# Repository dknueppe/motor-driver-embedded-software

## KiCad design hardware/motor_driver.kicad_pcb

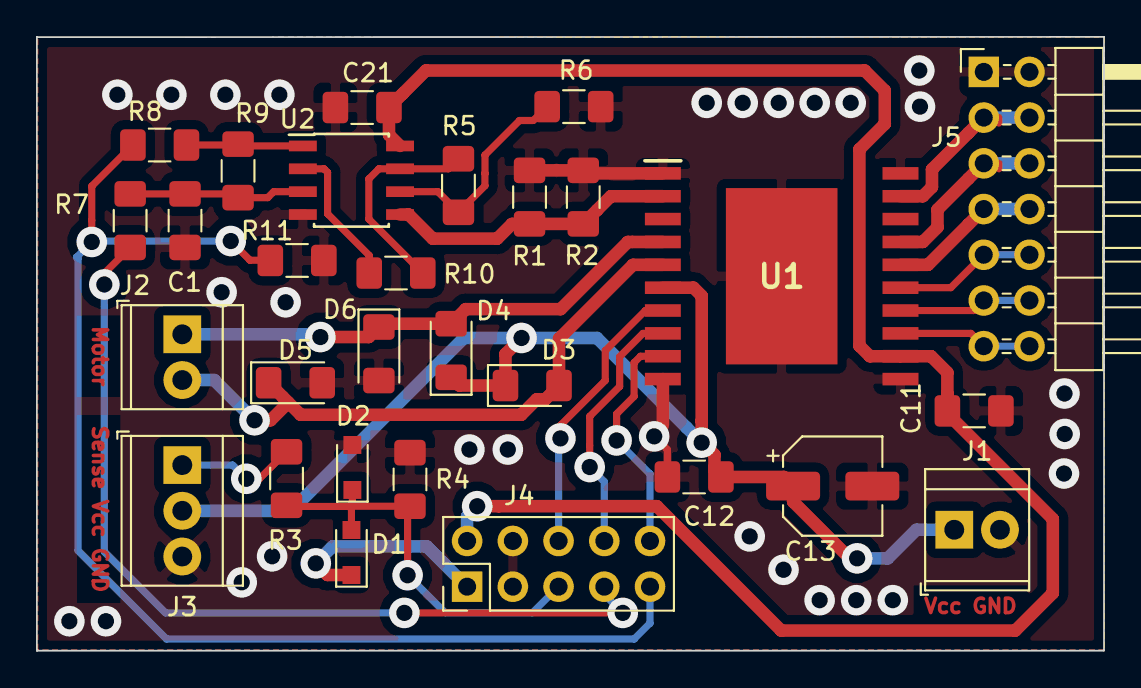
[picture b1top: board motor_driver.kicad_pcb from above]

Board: 2 copper layers, 59.3 x 34.1 mm, 29 parts (0 on the bottom side), 25 nets.

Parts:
C1: 16n; C_1206_3216Metric_Pad1.42x1.75mm_HandSolder
C11, C12, C21: 100n; C_1206_3216Metric_Pad1.42x1.75mm_HandSolder
C13: 10u; CP_Elec_5x4.5
D1, D2: D_Schottky; D_SOD-323_HandSoldering
D3, D4, D5, D6: D; D_1206_3216Metric_Pad1.42x1.75mm_HandSolder
J1, J2: Screw_Terminal_01x02; TerminalBlock_TE_282834-2_1x02_P2.54mm_Horizontal
J3: Screw_Terminal_01x03; TerminalBlock_TE_282834-3_1x03_P2.54mm_Horizontal
J4: Conn_02x05_Odd_Even; PinHeader_2x05_P2.54mm_Vertical
J5: Extension; PinHeader_2x07_P2.54mm_Horizontal
R1, R2: 200m; R_1206_3216Metric_Pad1.42x1.75mm_HandSolder
R3: 2.7k; R_1206_3216Metric_Pad1.42x1.75mm_HandSolder
R4, R6, R7, R10: 1k; R_1206_3216Metric_Pad1.42x1.75mm_HandSolder
R5, R11: 9k; R_1206_3216Metric_Pad1.42x1.75mm_HandSolder
R8: 4.7k; R_1206_3216Metric_Pad1.42x1.75mm_HandSolder
R9: 14.3k; R_1206_3216Metric_Pad1.42x1.75mm_HandSolder
U1: L298P; SOIC127P1420X360-21N
U2: LMV358; SOIC-8_3.9x4.9mm_P1.27mm

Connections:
+3V3: D1.1, J4.1
+5V: C11.1, C21.1, J4.2, U1.12, U2.8
+12V: C12.1, C13.1, D3.1, D4.1, J1.1, J3.2, U1.6
/COMP_IN: J4.7, R7.1
/COMP_OUT: J4.9, R8.2, R11.1
/ENABLE: J4.8, U1.8
/ENABLE_B: J5.11, J5.12, U1.14
/INPUT1: J4.6, U1.7
/INPUT2: J4.10, U1.9
/INPUT4: J5.9, J5.10, U1.15
/INPUT_3: J5.13, J5.14, U1.13
/OUT3: J5.7, J5.8, U1.16
/OUT4: J5.5, J5.6, U1.17
/PROX_OUT: D1.2, D2.1, J4.5, R3.2, R4.1
/SENSE_B: J5.3, J5.4, U1.19
GND: C1.2, C11.2, C12.2, C13.2, C21.2, D2.2, D5.2, D6.2, J1.2, J3.3, J4.3, J4.4, J5.1, J5.2, R1.2, R2.2, R4.2, R6.1, R11.2, U1.1, U1.10, U1.11, U1.20, U1.21, U2.4
unnamed: C1.1, R7.2, R9.2, U2.3
unnamed: D3.2, D5.1, J2.2, U1.5
unnamed: D4.2, D6.1, J2.1, U1.4
unnamed: J3.1, R3.1
unnamed: R1.1, R2.1, U1.2, U2.5
unnamed: R5.1, R6.2, U2.6
unnamed: R8.1, R9.1, U2.1
unnamed: R10.1, U2.2
unnamed: R5.2, R10.2, U2.7

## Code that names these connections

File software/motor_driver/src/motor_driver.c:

#include <wiringPi.h>
#include <stdio.h>
#include <stdbool.h>
#include <unistd.h>
#include "TimerObservable.h"
#include "PinObserver.h"
#include "PinObservable.h"
#include "FreqCounter.h"

/* Pin assignments from motor driver board to wiringPi internals */
#define INPUT1      3   /* connect YELLOW Wire with physical pin 15 (eigth on the inner row) */
#define INPUT2      5   /* connect RED Wire with physical pin 18 (ninth on the outer row) */
#define ENABLE      4   /* connect ORANGE Wire with physical pin 16 (eigth on the outer row) */
#define PROX_OUT    7   /* connect VIOLET Wire with physical pin 7 (fourth on the inner row) */
#define COMP_IN     1   /* connect BLUE Wire with physical pin 12 (sixth on the outer row) */
#define COMP_OUT    2   /* connect GREEN Wire with physical pin 13 (seventh on the inner row) */

int main()
{
    wiringPiSetup();

/* driving the motor */
    TimerObservable pwm = newTimerObservable(PWM_ENABLE);
    pwm->frequency = 440;
    pwm->dutyCycle = 100;
    PinObserver in1 = newPinObserver(INPUT1, LOW);
    PinObserver in2 = newPinObserver(INPUT2, LOW);
    pwm->clazz->observe((Observable)pwm, (void*)in1);
    pwm->clazz->start(pwm);

/* setup proximity sensor */
    PinObservable proximity_sensor = newPinObservable(PROX_OUT);
    FreqCounter freq_counter = newFreqCounter();
    proximity_sensor->clazz->observe((Observable)proximity_sensor, (void*)freq_counter);
    proximity_sensor->clazz->start(proximity_sensor);

/* setup voltage reference for current watchdog */
    pinMode(COMP_IN, PWM_OUTPUT);
    pwmSetClock(2);
    pwmSetRange(10);
    pwmWrite(1, 2);

/* setup motor current watchdog */
    PinObservable comp_out = newPinObservable(COMP_OUT);
    PinObserver enable = newPinObserver(ENABLE, HIGH);
    comp_out->clazz->observe((Observable)comp_out, (void*)enable);
    comp_out->clazz->start(comp_out);

    char tmp;
    while((tmp = getchar()) != 's') {
        printf("PRM: %.2f", freq_counter->clazz->getRPM(freq_counter));
        enable->pin->clazz->setPin(enable->pin, HIGH);
        if (tmp == 'r'){
            sem_wait(&(comp_out->_lock));
            sleep(1);
            sem_post(&(comp_out->_lock));
        }
    }

/* freeing up resources */
    pwm->clazz->join(pwm);
    proximity_sensor->clazz->join(proximity_sensor);
    comp_out->clazz->join(comp_out);
    deleteTimerObservable(pwm);
    deletePinObserver(in1);
    deletePinObserver(in2);
    deletePinObserver(enable);
    deletePinObservable(proximity_sensor);
    deletePinObservable(comp_out);
    deleteFreqCounter(freq_counter);
    return 0;
}

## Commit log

2019-12-27 init (mostly files from other repos)
2019-12-27 sync
2019-12-27 ramping up works
2020-01-04 updated schematics, and added code for freq counter
2020-01-04 well now at least
2020-01-04 cleanup
2020-01-04 Deleted software/WiringPi/wiringPi/wiringPi.h, software/WiringPi/wiringPi/wiringPiI2C.h, software/WiringPi/wiringPi/wiringPiSPI.h, software/WiringPi/wiringPi/wiringSerial.h files
2020-01-04 somewhat functional frequency counter, weird bugs in PinObserver tho
2020-01-04 frequency counter working
2020-01-06 working code
2020-01-06 renaming stuff to make more sense
2020-01-06 added setup for voltage reference
2020-01-06 code prepared for Praktikum
2020-01-13 added documentation
